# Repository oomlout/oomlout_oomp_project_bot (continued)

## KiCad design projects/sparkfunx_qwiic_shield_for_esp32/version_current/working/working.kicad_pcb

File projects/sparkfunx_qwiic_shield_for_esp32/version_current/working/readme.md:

# Qwiic_Shield_for_ESP32 by sparkfunX  
This is a harvested standardized copy of a project from github.  
The original project can be found at:  
https://github.com/sparkfunX/Qwiic_Shield_for_ESP32  
Please consult that link for additional, details, files, and license information.  
Note: It was auto harvested and if the original repo had more than one board file or anything out of the ordinary the files here are likely not representative.

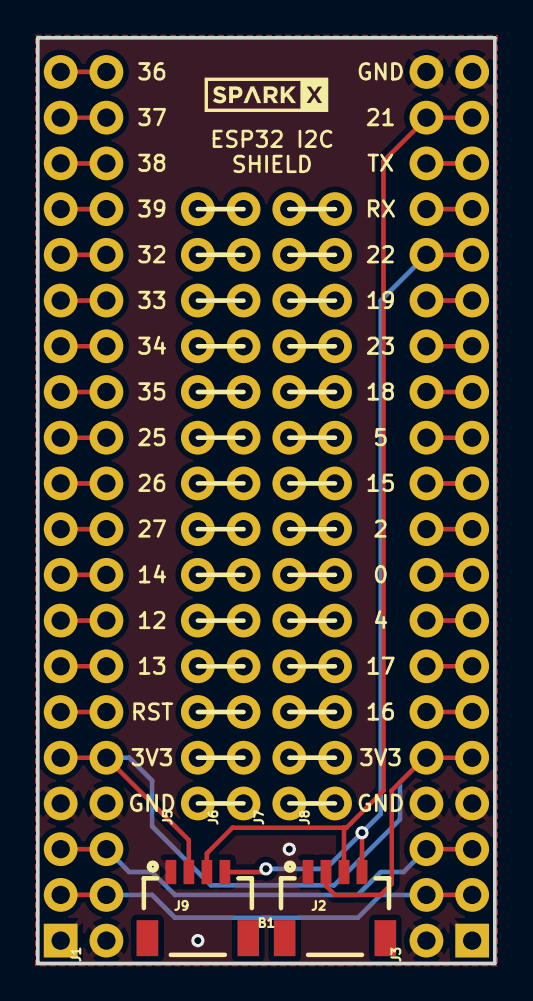
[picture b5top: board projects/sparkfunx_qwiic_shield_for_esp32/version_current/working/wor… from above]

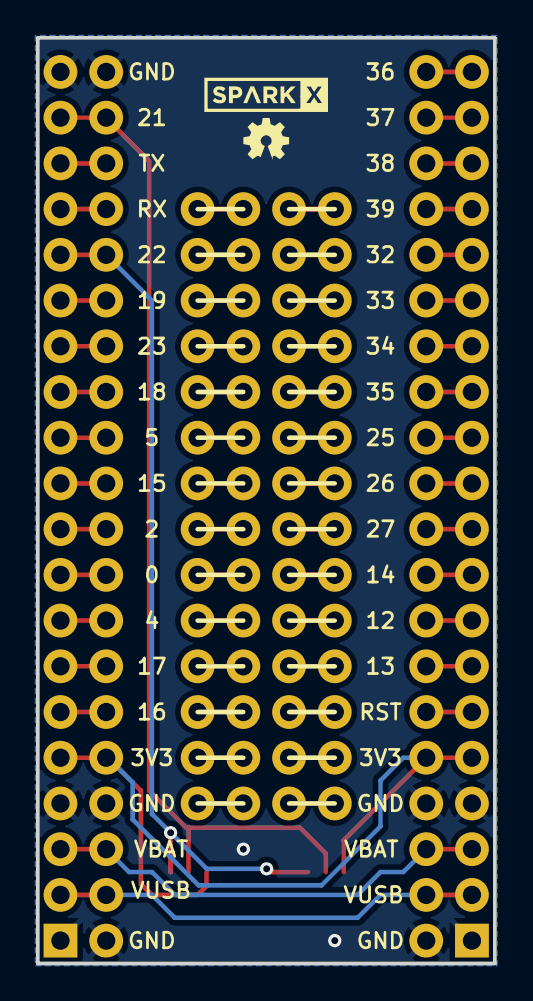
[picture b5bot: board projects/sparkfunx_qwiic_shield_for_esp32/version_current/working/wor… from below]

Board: 16 copper layers, 25.4 x 51.4 mm, 13 parts (2 on the bottom side), 61 nets.

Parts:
B1: ESP32_THING
FRAME1: FRAME-LETTERNO_PACKAGE; DUMMY
J1, J3: 1X20_NOSILK
J2, J9: 1X04_1MM_RA
J5, J6, J7, J8: 1X14_NO_SILK
LOGO1: OSHW-LOGOMINI; OSHW-LOGO-MINI
U$1, U$2: SPARKX-LOGO3; SPARKX-SMALL

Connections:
0: B1.32, J3.9
2: B1.31, J3.10
3.3V: B1.5, B1.36, J1.5, J2.2, J3.5, J9.2
4: B1.33, J3.8
5: B1.29, J3.12
12: B1.8, J1.8
13: B1.7, J1.7
14: B1.9, J1.9
15: B1.30, J3.11
16: B1.35, J3.6
17: B1.34, J3.7
25: B1.12, J1.12
26: B1.11, J1.11
27: B1.10, J1.10
32: B1.16, J1.16
33: B1.15, J1.15
34: B1.14, J1.14
35: B1.13, J1.13
36: B1.20, J1.20
37: B1.19, J1.19
38: B1.18, J1.18
39: B1.17, J1.17
GND: B1.1, B1.4, B1.21, B1.37, B1.40, J1.1, J1.4, J2.1, J3.1, J3.4, J3.20, J9.1
MISO: B1.26, J3.15
MOSI: B1.27, J3.14
unnamed: J7.1, J8.1
unnamed: J7.2, J8.2
unnamed: J7.3, J8.3
unnamed: J7.4, J8.4
unnamed: J7.5, J8.5
unnamed: J7.6, J8.6
unnamed: J7.7, J8.7
unnamed: J7.8, J8.8
unnamed: J7.9, J8.9
unnamed: J7.10, J8.10
unnamed: J7.11, J8.11
unnamed: J7.12, J8.12
unnamed: J7.13, J8.13
unnamed: J7.14, J8.14
unnamed: J5.1, J6.1
unnamed: J5.2, J6.2
unnamed: J5.3, J6.3
unnamed: J5.4, J6.4
unnamed: J5.5, J6.5
unnamed: J5.6, J6.6
unnamed: J5.7, J6.7
unnamed: J5.8, J6.8
unnamed: J5.9, J6.9
unnamed: J5.10, J6.10
unnamed: J5.11, J6.11
unnamed: J5.12, J6.12
unnamed: J5.13, J6.13
unnamed: J5.14, J6.14
RST: B1.6, J1.6
RX: B1.24, J3.17
SCK: B1.28, J3.13
SCL: B1.25, J2.4, J3.16, J9.4
SDA: B1.22, J2.3, J3.19, J9.3
TX: B1.23, J3.18
VBAT: B1.3, B1.38, J1.3, J3.3
VUSB: B1.2, B1.39, J1.2, J3.2

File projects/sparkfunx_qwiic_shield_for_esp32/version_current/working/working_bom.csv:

"Id";"Designator";"Footprint";"Quantity";"Designation";"Supplier and ref";
1;"J3,J1";"1X20_NOSILK";2;"";;;
2;"J2,J9";"1X04_1MM_RA";2;"";;;
3;"FRAME1";"DUMMY";1;"FRAME-LETTERNO_PACKAGE";;;
4;"J6,J7,J5,J8";"1X14_NO_SILK";4;"";;;
5;"B1";"ESP32_THING";1;"ESP32_THING";;;
6;"U$1,U$2";"SPARKX-SMALL";2;"SPARKX-LOGO3";;;
7;"LOGO1";"OSHW-LOGO-MINI";1;"OSHW-LOGOMINI";;;

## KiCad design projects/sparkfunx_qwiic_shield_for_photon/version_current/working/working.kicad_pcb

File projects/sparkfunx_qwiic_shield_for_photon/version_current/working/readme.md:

# OOMP Project  
## Qwiic_Shield_for_Photon  by sparkfunX  
  
oomp key: oomp_projects_flat_sparkfunx_qwiic_shield_for_photon  
(snippet of original readme)  
  
Qwiic Shield for Photon   
========================================  

[*SPX-14202*](https://www.sparkfun.com/products/14202)  
  
The Qwiic Shield for Photo connects the I<sup>2</sup>C bus (GND, 3.3V, SDA, and SCL) from the [Particle Photon](https://www.sparkfun.com/products/13774) to the SparkFun Qwiic system.   
  
License Information  
-------------------  
  
This product is _**open source**_!  
  
Please review the LICENSE.md file for license information.  
  
If you have any questions or concerns on licensing, please contact techsupport@sparkfun.com.  
  
Distributed as-is; no warranty is given.  
  
- Your friends at SparkFun.  
  
_<COLLABORATION CREDIT>_  
  
  full source readme at [readme_src.md](readme_src.md)  
  
source repo at: [https://github.com/sparkfunX/Qwiic_Shield_for_Photon](https://github.com/sparkfunX/Qwiic_Shield_for_Photon)  
## Board  

## Schematic  

[schematic pdf](working_schematic.pdf)  
## Images

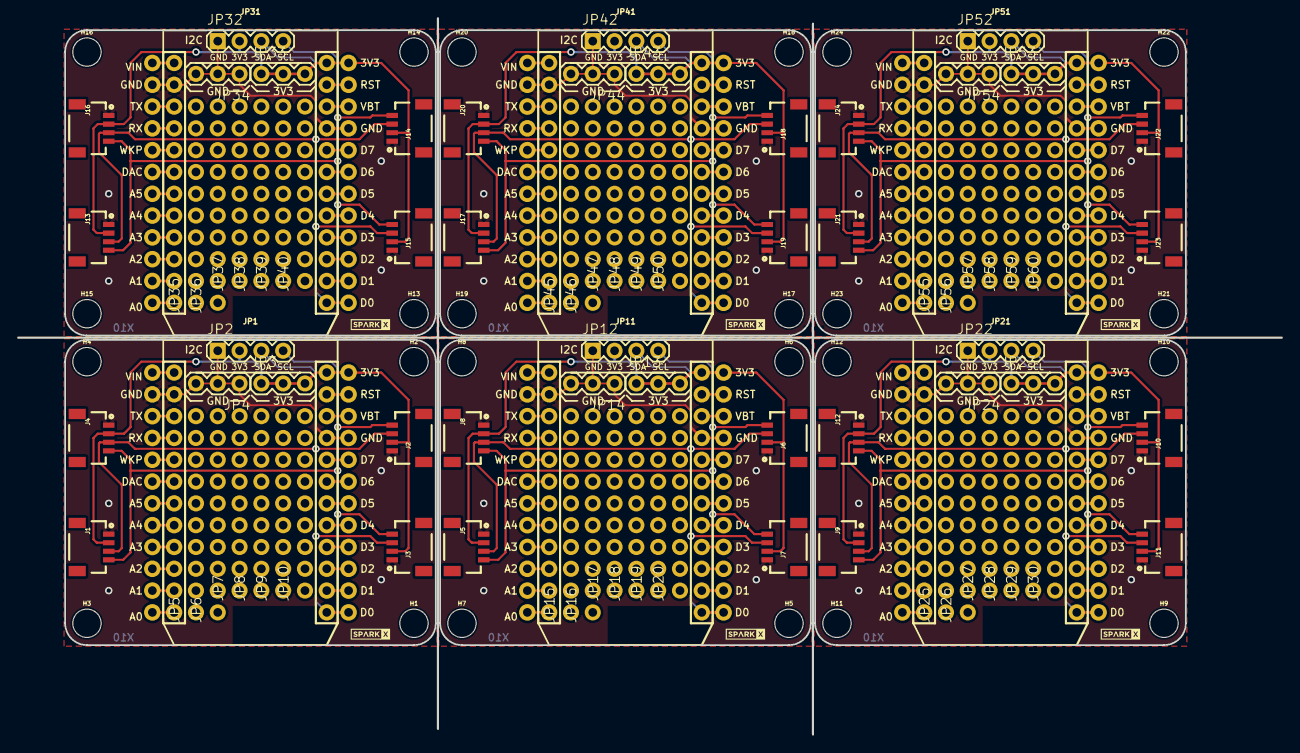
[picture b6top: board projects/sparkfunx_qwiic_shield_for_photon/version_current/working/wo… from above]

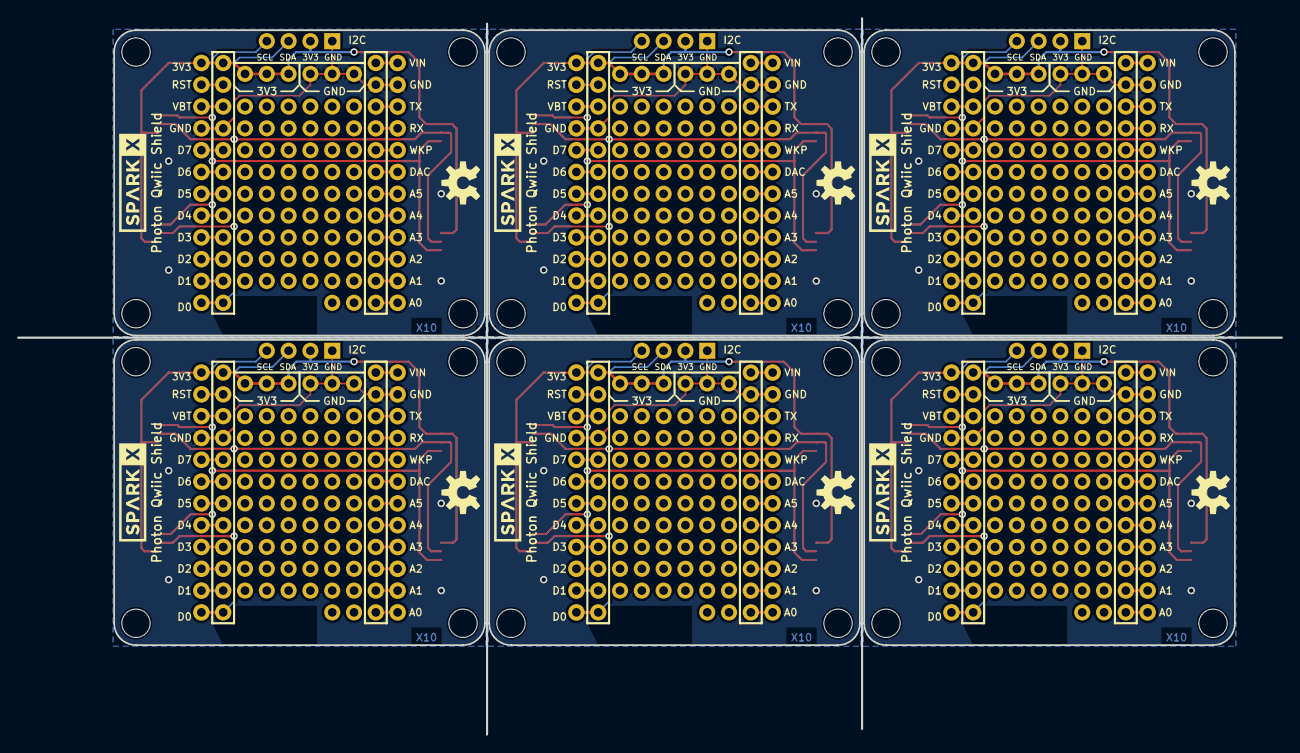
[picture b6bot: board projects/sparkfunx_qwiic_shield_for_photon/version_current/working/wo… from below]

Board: 2 copper layers, 147.2 x 83.4 mm, 126 parts (12 on the bottom side), 138 nets.

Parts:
H1, H2, H3, H4, H5, H6, H7, H8, H9, H10, H11, H12, H13, H14, H15, H16, H17, H18, H19, H20, H21, H22, H23, H24: STAND-OFF
J1, J2, J3, J4, J5, J6, J7, J8, J9, J10, J11, J12, J13, J14, J15, J16, J17, J18, J19, J20, J21, J22, J23, J24: 1X04_1MM_RA
JP1, JP11, JP21, JP31, JP41, JP51: PARTICLE_PHOTONTEMPLATE_NO_STANDOFF; PARTICLE_PHOTON_TEMPLATE_NO_STANDOFF
JP2, JP12, JP22, JP32, JP42, JP52: 1X04
JP3, JP4, JP13, JP14, JP23, JP24, JP33, JP34, JP43, JP44, JP53, JP54: 1X03
JP5, JP6, JP15, JP16, JP25, JP26, JP35, JP36, JP45, JP46, JP55, JP56: 1X10_NO_SILK
JP7, JP8, JP9, JP10, JP17, JP18, JP19, JP20, JP27, JP28, JP29, JP30, JP37, JP38, JP39, JP40, JP47, JP48, JP49, JP50, JP57, JP58, JP59, JP60: 1X09_NO_SILK
LOGO1, LOGO2, LOGO3, LOGO4, LOGO5, LOGO6: OSHW-LOGOM; OSHW-LOGO-M
U$1, U$2, U$5, U$7, U$9, U$11: SPARKX-TINY
U$3, U$4, U$6, U$8, U$10, U$12: SPARKX-LOGO5; SPARKX-LARGE

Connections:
A0: JP1.12, JP1.A0
A1: JP1.11, JP1.A1
A2: JP1.10, JP1.A2
A3: JP1.9, JP1.A3
A4: JP1.8, JP1.A4
A5: JP1.7, JP1.A5
A6: JP11.7, JP11.A5
A7: JP11.8, JP11.A4
A8: JP11.9, JP11.A3
A9: JP11.10, JP11.A2
A10: JP11.11, JP11.A1
A11: JP11.12, JP11.A0
A12: JP21.7, JP21.A5
A13: JP21.8, JP21.A4
A14: JP21.9, JP21.A3
A15: JP21.10, JP21.A2
A16: JP21.11, JP21.A1
A17: JP21.12, JP21.A0
A18: JP31.7, JP31.A5
A19: JP31.8, JP31.A4
A20: JP31.9, JP31.A3
A21: JP31.10, JP31.A2
A22: JP31.11, JP31.A1
A23: JP31.12, JP31.A0
A24: JP41.7, JP41.A5
A25: JP41.8, JP41.A4
A26: JP41.9, JP41.A3
A27: JP41.10, JP41.A2
A28: JP41.11, JP41.A1
A29: JP41.12, JP41.A0
A30: JP51.7, JP51.A5
A31: JP51.8, JP51.A4
A32: JP51.9, JP51.A3
A33: JP51.10, JP51.A2
A34: JP51.11, JP51.A1
A35: JP51.12, JP51.A0
D1: JP11.20, JP11.D7
D2: JP1.15, JP1.D2
D3: JP1.16, JP1.D3
D4: JP1.17, JP1.D4
D5: JP1.18, JP1.D5
D6: JP1.19, JP1.D6
D7: JP1.20, JP1.D7
D8: JP11.19, JP11.D6
D9: JP11.18, JP11.D5
D10: JP11.17, JP11.D4
D11: JP11.16, JP11.D3
D12: JP11.15, JP11.D2
D13: JP21.20, JP21.D7
D14: JP21.19, JP21.D6
D15: JP21.18, JP21.D5
D16: JP21.17, JP21.D4
D17: JP21.16, JP21.D3
D18: JP21.15, JP21.D2
D19: JP31.20, JP31.D7
D20: JP31.19, JP31.D6
D21: JP31.18, JP31.D5
D22: JP31.17, JP31.D4
D23: JP31.16, JP31.D3
D24: JP31.15, JP31.D2
D25: JP41.20, JP41.D7
D26: JP41.19, JP41.D6
D27: JP41.18, JP41.D5
D28: JP41.17, JP41.D4
D29: JP41.16, JP41.D3
D30: JP41.15, JP41.D2
D31: JP51.20, JP51.D7
D32: JP51.19, JP51.D6
D33: JP51.18, JP51.D5
D34: JP51.17, JP51.D4
D35: JP51.16, JP51.D3
D36: JP51.15, JP51.D2
DAC: JP1.6, JP1.DAC
DAC1: JP11.6, JP11.DAC
DAC2: JP21.6, JP21.DAC
DAC3: JP31.6, JP31.DAC
DAC4: JP41.6, JP41.DAC
DAC5: JP51.6, JP51.DAC
GND: J1.1, J2.1, J3.1, J4.1, JP1.2, JP1.21, JP1.GND@0, JP1.GND@2, JP2.1, JP4.1, JP4.2, JP4.3
GND1: J5.1, J6.1, J7.1, J8.1, JP11.2, JP11.21, JP11.GND@0, JP11.GND@2, JP12.1, JP14.1, JP14.2, JP14.3
GND2: J9.1, J10.1, J11.1, J12.1, JP21.2, JP21.21, JP21.GND@0, JP21.GND@2, JP22.1, JP24.1, JP24.2, JP24.3
GND3: J13.1, J14.1, J15.1, J16.1, JP31.2, JP31.21, JP31.GND@0, JP31.GND@2, JP32.1, JP34.1, JP34.2, JP34.3
GND4: J17.1, J18.1, J19.1, J20.1, JP41.2, JP41.21, JP41.GND@0, JP41.GND@2, JP42.1, JP44.1, JP44.2, JP44.3
GND5: J21.1, J22.1, J23.1, J24.1, JP51.2, JP51.21, JP51.GND@0, JP51.GND@2, JP52.1, JP54.1, JP54.2, JP54.3
RST: JP1.23, JP1.RST
RST1: JP11.23, JP11.RST
RST2: JP21.23, JP21.RST
RST3: JP31.23, JP31.RST
RST4: JP41.23, JP41.RST
RST5: JP51.23, JP51.RST
RX: JP1.4, JP1.RX
RX1: JP11.4, JP11.RX
RX2: JP21.4, JP21.RX
RX3: JP31.4, JP31.RX
RX4: JP41.4, JP41.RX
RX5: JP51.4, JP51.RX
SCL: J1.4, J2.4, J3.4, J4.4, JP1.14, JP1.D1, JP2.4
SCL1: J5.4, J6.4, J7.4, J8.4, JP11.14, JP11.D1, JP12.4
SCL2: J9.4, J10.4, J11.4, J12.4, JP21.14, JP21.D1, JP22.4
SCL3: J13.4, J14.4, J15.4, J16.4, JP31.14, JP31.D1, JP32.4
SCL4: J17.4, J18.4, J19.4, J20.4, JP41.14, JP41.D1, JP42.4
SCL5: J21.4, J22.4, J23.4, J24.4, JP51.14, JP51.D1, JP52.4
SDA: J1.3, J2.3, J3.3, J4.3, JP1.13, JP1.D0, JP2.3
SDA1: J5.3, J6.3, J7.3, J8.3, JP11.13, JP11.D0, JP12.3
SDA2: J9.3, J10.3, J11.3, J12.3, JP21.13, JP21.D0, JP22.3
SDA3: J13.3, J14.3, J15.3, J16.3, JP31.13, JP31.D0, JP32.3
SDA4: J17.3, J18.3, J19.3, J20.3, JP41.13, JP41.D0, JP42.3
SDA5: J21.3, J22.3, J23.3, J24.3, JP51.13, JP51.D0, JP52.3
TX: JP1.3, JP1.TX
TX1: JP11.3, JP11.TX
TX2: JP21.3, JP21.TX
TX3: JP31.3, JP31.TX
TX4: JP41.3, JP41.TX
TX5: JP51.3, JP51.TX
VBAT: JP1.22, JP1.VBAT
VBAT1: JP11.22, JP11.VBAT
VBAT2: JP21.22, JP21.VBAT
VBAT3: JP31.22, JP31.VBAT
VBAT4: JP41.22, JP41.VBAT
VBAT5: JP51.22, JP51.VBAT
VCC: J1.2, J2.2, J3.2, J4.2, JP1.3V3, JP1.24, JP2.2, JP3.1, JP3.2, JP3.3
VCC1: J5.2, J6.2, J7.2, J8.2, JP11.3V3, JP11.24, JP12.2, JP13.1, JP13.2, JP13.3
VCC2: J9.2, J10.2, J11.2, J12.2, JP21.3V3, JP21.24, JP22.2, JP23.1, JP23.2, JP23.3
VCC3: J13.2, J14.2, J15.2, J16.2, JP31.3V3, JP31.24, JP32.2, JP33.1, JP33.2, JP33.3
VCC4: J17.2, J18.2, J19.2, J20.2, JP41.3V3, JP41.24, JP42.2, JP43.1, JP43.2, JP43.3
VCC5: J21.2, J22.2, J23.2, J24.2, JP51.3V3, JP51.24, JP52.2, JP53.1, JP53.2, JP53.3
VIN: JP1.1, JP1.VIN
VIN1: JP11.1, JP11.VIN
VIN2: JP21.1, JP21.VIN
VIN3: JP31.1, JP31.VIN
VIN4: JP41.1, JP41.VIN
VIN5: JP51.1, JP51.VIN
WKP: JP1.5, JP1.WKP
WKP1: JP11.5, JP11.WKP
WKP2: JP21.5, JP21.WKP
WKP3: JP31.5, JP31.WKP
WKP4: JP41.5, JP41.WKP
WKP5: JP51.5, JP51.WKP

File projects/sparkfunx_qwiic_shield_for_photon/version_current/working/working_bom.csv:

"Id";"Designator";"Footprint";"Quantity";"Designation";"Supplier and ref";
1;"J9,J22,J5,J3,J13,J17,J1,J12,J19,J8,J24,J11,J18,J20,J15,J14,J10,J16,J6,J2,J7,J23,J4,J21";"1X04_1MM_RA";24;"";;;
2;"H17,H3,H23,H21,H8,H7,H9,H24,H22,H18,H20,H16,H11,H10,H13,H6,H12,H19,H14,H4,H1,H2,H5,H15";"STAND-OFF";24;"STAND-OFF";;;
3;"JP54,JP13,JP24,JP3,JP14,JP53,JP44,JP34,JP4,JP33,JP43,JP23";"1X03";12;"";;;
4;"JP56,JP46,JP55,JP25,JP5,JP15,JP16,JP6,JP35,JP36,JP26,JP45";"1X10_NO_SILK";12;"";;;
5;"JP9,JP49,JP10,JP48,JP57,JP38,JP58,JP60,JP50,JP8,JP30,JP18,JP17,JP20,JP47,JP28,JP27,JP39,JP19,JP40,JP29,JP7,JP37,JP59";"1X09_NO_SILK";24;"";;;
6;"JP22,JP12,JP2,JP52,JP42,JP32";"1X04";6;"";;;
7;"JP41,JP21,JP31,JP11,JP1,JP51";"PARTICLE_PHOTON_TEMPLATE_NO_STANDOFF";6;"PARTICLE_PHOTONTEMPLATE_NO_STANDOFF";;;
8;"U$1,U$5,U$7,U$9,U$2,U$11";"SPARKX-TINY";6;"";;;
9;"U$3,U$8,U$4,U$10,U$12,U$6";"SPARKX-LARGE";6;"SPARKX-LOGO5";;;
10;"LOGO4,LOGO2,LOGO1,LOGO6,LOGO5,LOGO3";"OSHW-LOGO-M";6;"OSHW-LOGOM";;;

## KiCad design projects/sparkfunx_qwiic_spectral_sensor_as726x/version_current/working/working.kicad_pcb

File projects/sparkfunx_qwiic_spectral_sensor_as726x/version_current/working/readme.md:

# Qwiic_Spectral_Sensor-AS726x by sparkfunX  
This is a harvested standardized copy of a project from github.  
The original project can be found at:  
https://github.com/sparkfunX/Qwiic_Spectral_Sensor-AS726x  
Please consult that link for additional, details, files, and license information.  
Note: It was auto harvested and if the original repo had more than one board file or anything out of the ordinary the files here are likely not representative.

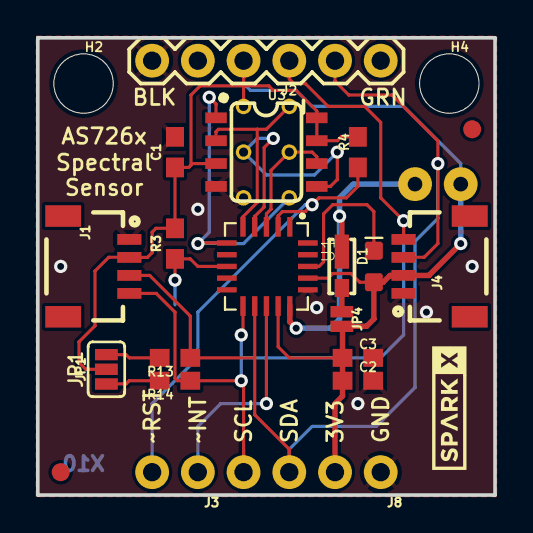
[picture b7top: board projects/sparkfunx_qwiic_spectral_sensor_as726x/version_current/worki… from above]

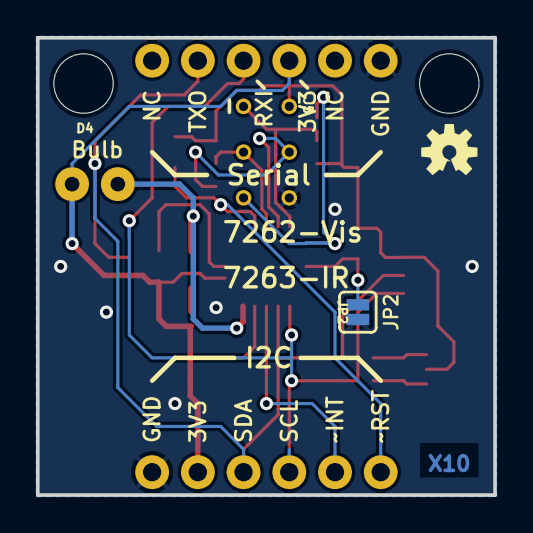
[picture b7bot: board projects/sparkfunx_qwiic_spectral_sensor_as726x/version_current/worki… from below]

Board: 2 copper layers, 25.4 x 25.4 mm, 28 parts (4 on the bottom side), 16 nets.

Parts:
C1, C2: 1.0uF; 0603
C3: 10uF; 0603
D1: BLUE; LED-0603
D2: 5700k; SUPER_BRIGHT_SMD_LED_1206
D4: Incandescent; LED_5MM_NOSILK
FD1, FD2: FIDUCIAL1X2; FIDUCIAL-1X2
FRAME1: FRAME-LETTER; CREATIVE_COMMONS
H2, H4: STAND-OFF
J1, J4: 1X04_1MM_RA
J2: Serial Interface; FTDI_BASIC
J3: 1X02_NO_SILK
J5: Flash Programming; 2X3_TEST_POINTS
J8: 1X04_NO_SILK
JP1: SMT-JUMPER_3_2-NC_PASTE_SILK
JP2: SMT-JUMPER_2_NO_SILK
JP4: SMT-JUMPER_2_NC_PASTE_NO-SILK
LOGO4: OSHW-LOGOS; OSHW-LOGO-S
R3, R4: 10k; 0603
R13, R14: 4.7k; 0603
U1: AS726X; LGA20
U3: 4MB Flash; SO08
U$1: SPARKX-LOGO3; SPARKX-SMALL

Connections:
3.3V: C1.1, C2.1, C3.1, D1.A, D4.A, J1.2, J2.VCC, J4.2, J5.2, J8.2, JP1.2, JP4.2, R3.2, R4.2, U1.14, U1.17, U3.3, U3.7, U3.8
GND: C1.2, C2.2, C3.2, J1.1, J2.GND, J4.1, J5.6, J8.1, JP2.1, U1.16, U3.4
LED_DRV: D2.C, D4.K, U1.15
MISO: J5.1, U1.5, U3.2
MOSI: J5.4, U1.4, U3.5
unnamed: JP2.2, R3.1, U1.8
unnamed: D1.C, U1.18
unnamed: JP1.3, R13.2
unnamed: JP1.1, R14.2
unnamed: D2.A, JP4.1
RX/SCL: J1.4, J2.TXO, J4.4, J8.4, R14.1, U1.11
SCK: J5.3, U1.3, U3.6
TX/SDA: J1.3, J2.RXI, J4.3, J8.3, R13.1, U1.12
~CS_EE: J5.5, U1.6, U3.1
~INT: J3.1, U1.13
~RST: J3.2, R4.1, U1.2

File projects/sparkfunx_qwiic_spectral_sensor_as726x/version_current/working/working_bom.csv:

"Id";"Designator";"Footprint";"Quantity";"Designation";"Supplier and ref";
1;"J3";"1X02_NO_SILK";1;"";;;
2;"U1";"LGA20";1;"AS726X";;;
3;"J1,J4";"1X04_1MM_RA";2;"";;;
4;"FD2,FD1";"FIDUCIAL-1X2";2;"FIDUCIAL1X2";;;
5;"C2,C1";"0603";2;"1.0uF";;;
6;"R13,R14";"0603";2;"4.7k";;;
7;"R3,R4";"0603";2;"10k";;;
8;"D2";"SUPER_BRIGHT_SMD_LED_1206";1;"5700k";;;
9;"JP4";"SMT-JUMPER_2_NC_PASTE_NO-SILK";1;"";;;
10;"C3";"0603";1;"10uF";;;
11;"J2";"FTDI_BASIC";1;"Serial Interface";;;
12;"H4,H2";"STAND-OFF";2;"STAND-OFF";;;
13;"U3";"SO08";1;"4MB Flash";;;
14;"JP1";"SMT-JUMPER_3_2-NC_PASTE_SILK";1;"";;;
15;"D1";"LED-0603";1;"BLUE";;;
16;"U$1";"SPARKX-SMALL";1;"SPARKX-LOGO3";;;
17;"J8";"1X04_NO_SILK";1;"";;;
18;"FRAME1";"CREATIVE_COMMONS";1;"FRAME-LETTER";;;
19;"J5";"2X3_TEST_POINTS";1;"Flash Programming";;;
20;"D4";"LED_5MM_NOSILK";1;"Incandescent";;;
21;"LOGO4";"OSHW-LOGO-S";1;"OSHW-LOGOS";;;
22;"JP2";"SMT-JUMPER_2_NO_SILK";1;"";;;

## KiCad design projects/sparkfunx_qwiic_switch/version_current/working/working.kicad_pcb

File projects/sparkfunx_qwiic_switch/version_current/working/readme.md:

# Qwiic_Switch by sparkfunX  
This is a harvested standardized copy of a project from github.  
The original project can be found at:  
https://github.com/sparkfunX/Qwiic_Switch  
Please consult that link for additional, details, files, and license information.  
Note: It was auto harvested and if the original repo had more than one board file or anything out of the ordinary the files here are likely not representative.

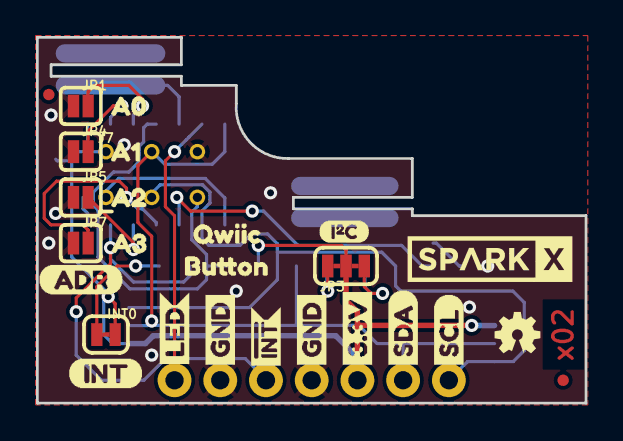
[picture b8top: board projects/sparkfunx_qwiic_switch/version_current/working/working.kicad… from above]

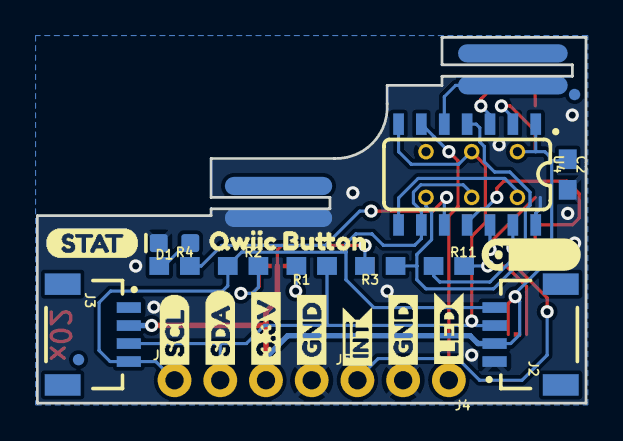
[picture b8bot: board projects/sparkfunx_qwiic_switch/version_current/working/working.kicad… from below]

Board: 2 copper layers, 30.5 x 20.3 mm, 54 parts (27 on the bottom side), 17 nets.

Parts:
C2: 0.1uF; 0603
D1: RED; LED-0603
FRAME1: FRAME-LETTER; CREATIVE_COMMONS
INT0: SMT-JUMPER_2_NC_TRACE_SILK
J1: 1X04_NO_SILK
J2, J3: JST04_1MM_RA
J4: 1X02_NO_SILK
J5: 1X01_NO_SILK
J7: ISP; 2X3_TEST_POINTS
JP1, JP4, JP5, JP7: SMT-JUMPER_2_NO_SILK
JP2, JP6, JP8, JP9: FIDUCIALUFIDUCIAL; MICRO-FIDUCIAL
JP3: SMT-JUMPER_3_2-NC_TRACE_SILK
LOGO1: OSHW-LOGOMINI; OSHW-LOGO-MINI
R1, R2: 2.2k; 0603
R3, R11: 10k; 0603
R4: 1k; 0603
U4: ATTINY84-ARDUINO; SO14
U$1: QWIIC_5.5MM
U$2, U$20: QWIIC0
U$3, U$19: LED2
U$4: INT-()-04
U$5, U$14: SCL
U$6, U$12: SDA
U$7, U$22: 3.3V
U$8, U$13, U$16, U$17: GND
U$9: (ADR)
U$10: I_SUPER2_C-()-03
U$11, U$15: INT#-[_-04
U$18: SPARKX-MEDIUM
U$21: STAT1
U$23, U$24: BUTTON1
U$25: A00
U$26: A11
U$27: A22
U$28: A33

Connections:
3.3V: C2.1, INT0.2, J1.3, J2.2, J3.2, J7.2, JP3.2, R3.2, U4.1
ADR0: JP1.2, U4.3
ADR1: JP4.2, U4.2
ADR2: JP5.2, U4.12
ADR3: JP7.2, U4.11
GND: C2.2, D1.C, J1.4, J2.1, J3.1, J4.2, J7.6, JP1.1, JP4.1, JP5.1, JP7.1, U4.14
INT_R: INT0.1, R11.2
LED: J4.1, U4.6
MISO: J7.1, U4.8
unnamed: D1.A, R4.1
SCL: J1.1, J2.4, J3.4, J7.3, R2.1, U4.9
SCL_PU1: JP3.1, R2.2
SDA: J1.2, J2.3, J3.3, J7.4, R1.1, U4.7
SDA_PU1: JP3.3, R1.2
STAT: R4.2, U4.10
~INT: J5.1, R11.1, U4.13
~RST: J7.5, R3.1, U4.4

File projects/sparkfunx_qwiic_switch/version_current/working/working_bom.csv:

"Id";"Designator";"Footprint";"Quantity";"Designation";"Supplier and ref";
1;"JP4,JP5,JP7,JP1";"SMT-JUMPER_2_NO_SILK";4;"";;;
2;"U$8,U$17,U$16,U$13";"GND";4;"";;;
3;"U$10";"I_SUPER2_C-()-03";1;"";;;
4;"U$18";"SPARKX-MEDIUM";1;"";;;
5;"U$6,U$12";"SDA";2;"";;;
6;"U$20,U$2";"QWIIC0";2;"";;;
7;"JP2,JP6,JP8,JP9";"MICRO-FIDUCIAL";4;"FIDUCIALUFIDUCIAL";;;
8;"U$7,U$22";"3.3V";2;"";;;
9;"JP3";"SMT-JUMPER_3_2-NC_TRACE_SILK";1;"";;;
10;"U$4";"INT-()-04";1;"";;;
11;"LOGO1";"OSHW-LOGO-MINI";1;"OSHW-LOGOMINI";;;
12;"U$27";"A22";1;"";;;
13;"U$19,U$3";"LED2";2;"";;;
14;"J7";"2X3_TEST_POINTS";1;"ISP";;;
15;"U$9";"(ADR)";1;"";;;
16;"U$15,U$11";"INT#-[_-04";2;"";;;
17;"U$28";"A33";1;"";;;
18;"U$25";"A00";1;"";;;
19;"U$24,U$23";"BUTTON1";2;"";;;
20;"U$26";"A11";1;"";;;
21;"INT0";"SMT-JUMPER_2_NC_TRACE_SILK";1;"";;;
22;"U$5,U$14";"SCL";2;"";;;
23;"U4";"SO14";1;"ATTINY84-ARDUINO";;;
24;"R11,R3";"0603";2;"10k";;;
25;"J4";"1X02_NO_SILK";1;"";;;
26;"J1";"1X04_NO_SILK";1;"";;;
27;"U$1";"QWIIC_5.5MM";1;"";;;
28;"D1";"LED-0603";1;"RED";;;
29;"J3,J2";"JST04_1MM_RA";2;"";;;
30;"FRAME1";"CREATIVE_COMMONS";1;"FRAME-LETTER";;;
31;"R4";"0603";1;"1k";;;
32;"R2,R1";"0603";2;"2.2k";;;
33;"U$21";"STAT1";1;"";;;
34;"J5";"1X01_NO_SILK";1;"";;;
35;"C2";"0603";1;"0.1uF";;;
